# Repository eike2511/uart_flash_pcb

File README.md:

# UART flash PCB

## Features:
- flash µC over UART
	- ESP8266
	- ESP32
	- ATMEGA
	- intigrated slot for ESP8266-01
- intigrated RST and flash button
	- with LEDs and labelling
	- jumper for manual and auto mode
- Reverse polarity protected pin tray
- Three different USB sockets
	- mini USB B
	- micro USB B
	- USB C
- Vcc = 5V  or 3.3V 
	- with LEDs and labelling
	- jumper for selection
	- 5V from USB Bus
	- 3.3V from additional linear regulator in connection with internal regulator of the FT232,  with up to 800mA
- LEDs at TXD and RXD for visual control of the UART connection

## Hardware:
Gerber and drilling data are in the repository. [Component placement](./uart_flash_pcb_ibom.html)

## Software:
No stand-alone software is needed. Use esptool.py or e.g. VS Code for programming.

## Usage:
1. Connect USB
2. Connect the correct jumpers for 5V or 3.3V
3. Connect the jumpers for auto-flash and auto-RST or use the button
4. Connect the device to be flashed or plug in an ESP-01
5. be save the TXD and RXD are crossed

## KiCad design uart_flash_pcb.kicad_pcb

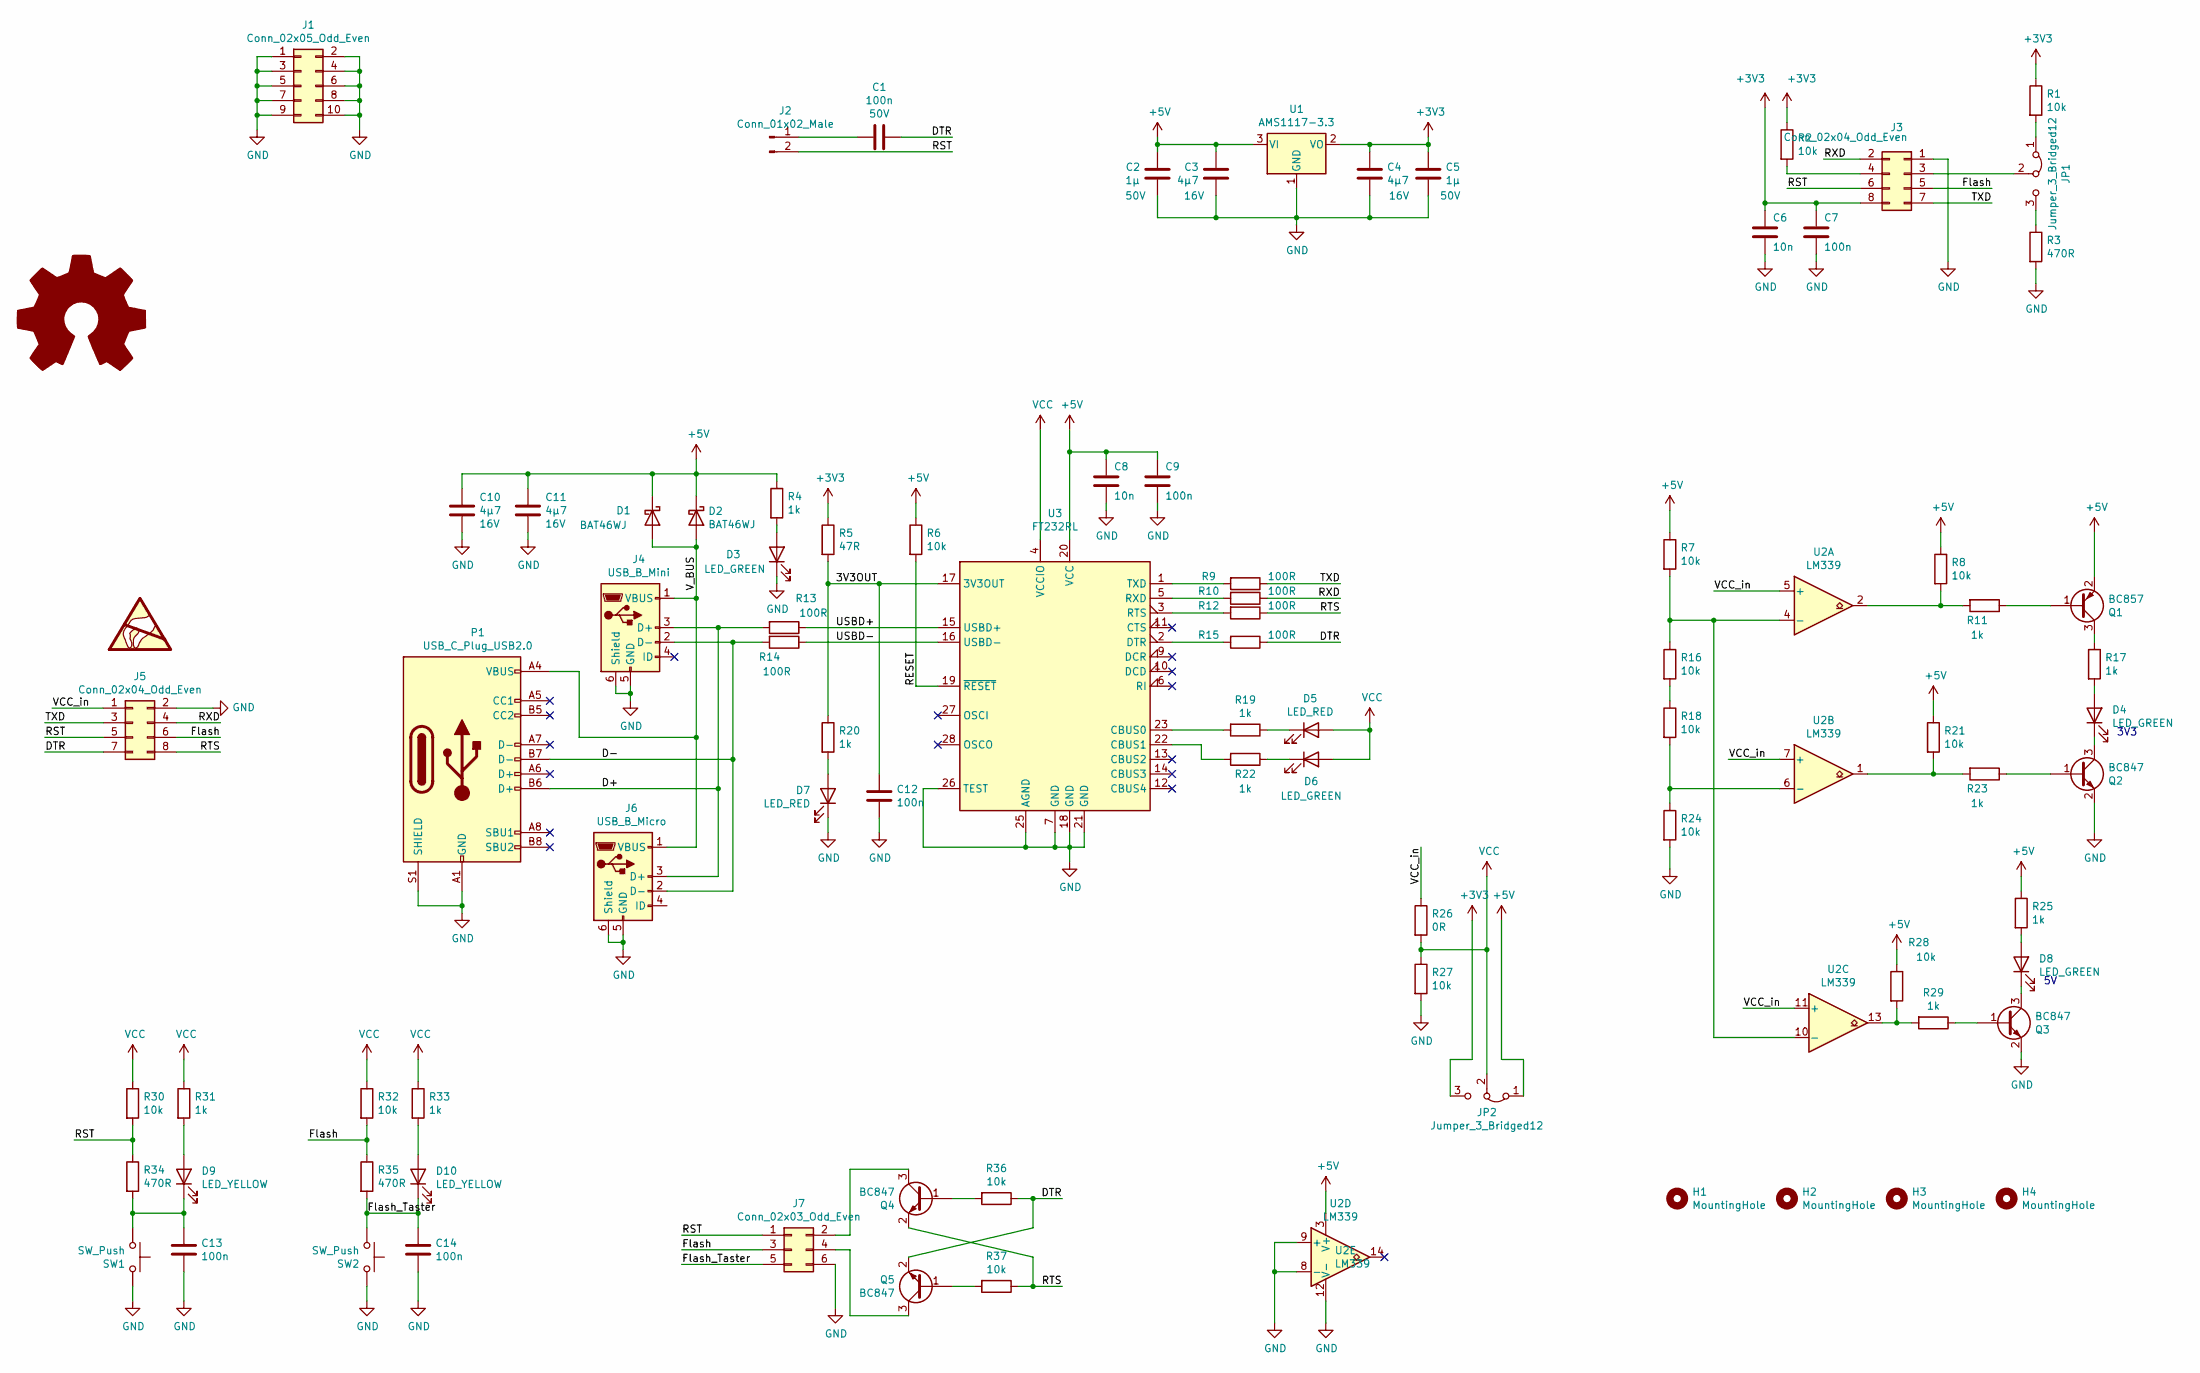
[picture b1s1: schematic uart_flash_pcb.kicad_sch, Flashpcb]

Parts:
C1, C7, C9, C12, C13, C14: 100n; C_0805_2012Metric
C2, C5: 1µ; C_0805_2012Metric
C3, C4, C10, C11: 4µ7; C_1206_3216Metric
C6, C8: 10n; C_0805_2012Metric
D1, D2: BAT46WJ; D_SOD-323
D3, D4, D6, D8: LED_GREEN; LED_0805_2012Metric
D5, D7: LED_RED; LED_0805_2012Metric
D9, D10: LED_YELLOW; LED_0805_2012Metric
H1, H2, H3, H4: MountingHole; MountingHole_3.2mm_M3
J1: Conn_02x05_Odd_Even; PinHeader_2x05_P2.54mm_Vertical
J2: Conn_01x02_Male; PinHeader_1x02_P2.54mm_Vertical
J3: Conn_02x04_Odd_Even; PinSocket_2x04_P2.54mm_Vertical
J4: USB_B_Mini; USB_Mini-B_Wuerth_65100516121_Horizontal
J5: Conn_02x04_Odd_Even; PinHeader_2x04_P2.54mm_Vertical
J6: USB_B_Micro; USB_Micro-B_Molex_47346-0001
J7: Conn_02x03_Odd_Even; PinHeader_2x03_P2.54mm_Vertical
JP1, JP2: Jumper_3_Bridged12; PinHeader_1x03_P2.54mm_Vertical
P1: USB_C_Plug_USB2.0; USB_C_Receptacle_XKB_U262-16XN-4BVC11
Q1: BC857; SOT-23
Q2, Q3, Q4, Q5: BC847; SOT-23
R1, R2, R6, R7, R8, R16, R18, R21, R24, R27, R28, R30, R32, R36, R37: 10k; R_0805_2012Metric
R3, R34, R35: 470R; R_0805_2012Metric
R4, R11, R17, R19, R20, R22, R23, R25, R29, R31, R33: 1k; R_0805_2012Metric
R5: 47R; R_0805_2012Metric
R9, R10, R12, R13, R14, R15: 100R; R_0805_2012Metric
R26: 0R; R_0805_2012Metric
SW1, SW2: SW_Push; SW_Push_SPST_4x3x2
U1: AMS1117-3.3; SOT-223-3_TabPin2
U2: LM339; SOIC-14_3.9x8.7mm_P1.27mm
U3: FT232RL; SSOP-28_5.3x10.2mm_P0.65mm

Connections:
+3V3: C4.1, C5.1, C6.1, C7.1, J3.8, JP2.3 (B), R1.1, R2.1, R5.1, U1.2 (VO)
+5V: C2.1, C3.1, C8.1, C9.1, C10.1, C11.1, D1.1 (K), D2.1 (K), JP2.1 (A), Q1.2 (E), R4.1, R6.1, R7.1, R8.1, R21.1, R25.1, R28.1, U1.3 (VI), U2.3 (V+), U3.20 (VCC)
/3V3OUT: C12.1, R5.2, R20.1, U3.17 (3V3OUT)
/D+: J4.3 (D+), J6.3 (D+), P1.B6 (D+), R13.2
/D-: J4.2 (D-), J6.2 (D-), P1.B7 (D-), R14.2
/DTR: C1.1, J5.7, Q5.2 (E), R15.1, R36.1
/Flash: J3.5, J5.6, J7.3, R32.2, R35.1
/Flash_Taster: C14.1, D10.1 (K), J7.5, R35.2, SW2.1
/RESET: R6.2, U3.19 (~RESET)
/RST: J2.2, J3.6, J5.5, J7.1, R30.2, R34.1
/RTS: J5.8, Q4.2 (E), R12.1, R37.1
/RXD: J3.2, J5.4, R10.1
/TXD: J3.7, J5.3, R9.1
/USBD+: R13.1, U3.15 (USBD+)
/USBD-: R14.1, U3.16 (USBD-)
/VCC_in: J5.1, R26.1, U2.5 (+), U2.7 (+), U2.11 (+)
/V_BUS: D1.2 (A), D2.2 (A), J4.1 (VBUS), J6.1 (VBUS), P1.A4 (VBUS), P1.A9 (VBUS), P1.B4 (VBUS), P1.B9 (VBUS)
GND: C2.2, C3.2, C4.2, C5.2, C6.2, C7.2, C8.2, C9.2, C10.2, C11.2, C12.2, C13.2, C14.2, D3.1 (K), D7.1 (K), J1.1, J1.2, J1.3, J1.4, J1.5, J1.6, J1.7, J1.8, J1.9, J1.10, J3.1, J4.5 (GND), J4.6 (Shield), J5.2, J6.5 (GND), J6.6 (Shield), J7.6, P1.A1 (GND), P1.A12 (GND), P1.B1 (GND), P1.B12 (GND), P1.S1 (SHIELD), Q2.2 (E), Q3.2 (E), R3.2, R24.2, R27.2, SW1.2, SW2.2, U1.1 (GND), U2.8 (-), U2.9 (+), U2.12 (V-), U3.7 (GND), U3.18 (GND), U3.21 (GND), U3.25 (AGND), U3.26 (TEST)
unnamed: C1.2, J2.1
unnamed: C13.1, D9.1 (K), R34.2, SW1.1
unnamed: D3.2 (A), R4.2
unnamed: D4.1 (K), Q2.3 (C)
unnamed: D4.2 (A), R17.2
unnamed: D5.1 (K), R19.1
unnamed: D6.1 (K), R22.1
unnamed: D7.2 (A), R20.2
unnamed: D8.1 (K), Q3.3 (C)
unnamed: D8.2 (A), R25.2
unnamed: D9.2 (A), R31.2
unnamed: D10.2 (A), R33.2
unnamed: J3.3, JP1.2 (C)
unnamed: J3.4, R2.2
unnamed: J7.2, Q4.3 (C)
unnamed: J7.4, Q5.3 (C)
unnamed: JP1.1 (A), R1.2
unnamed: JP1.3 (B), R3.1
unnamed: Q1.1 (B), R11.1
unnamed: Q1.3 (C), R17.1
unnamed: Q2.1 (B), R23.1
unnamed: Q3.1 (B), R29.1
unnamed: Q4.1 (B), R36.2
unnamed: Q5.1 (B), R37.2
unnamed: R9.2, U3.1 (TXD)
unnamed: R10.2, U3.5 (RXD)
unnamed: R8.2, R11.2, U2.2
unnamed: R12.2, U3.3 (RTS)
unnamed: R15.2, U3.2 (DTR)
unnamed: R7.2, R16.1, U2.4 (-), U2.10 (-)
unnamed: R16.2, R18.1
unnamed: R18.2, R24.1, U2.6 (-)
unnamed: R19.2, U3.23 (CBUS0)
unnamed: R21.2, R23.2, U2.1
unnamed: R22.2, U3.22 (CBUS1)
unnamed: R28.2, R29.2, U2.13
VCC: D5.2 (A), D6.2 (A), JP2.2 (C), R26.2, R27.1, R30.1, R31.1, R32.1, R33.1, U3.4 (VCCIO)

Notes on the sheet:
3V3

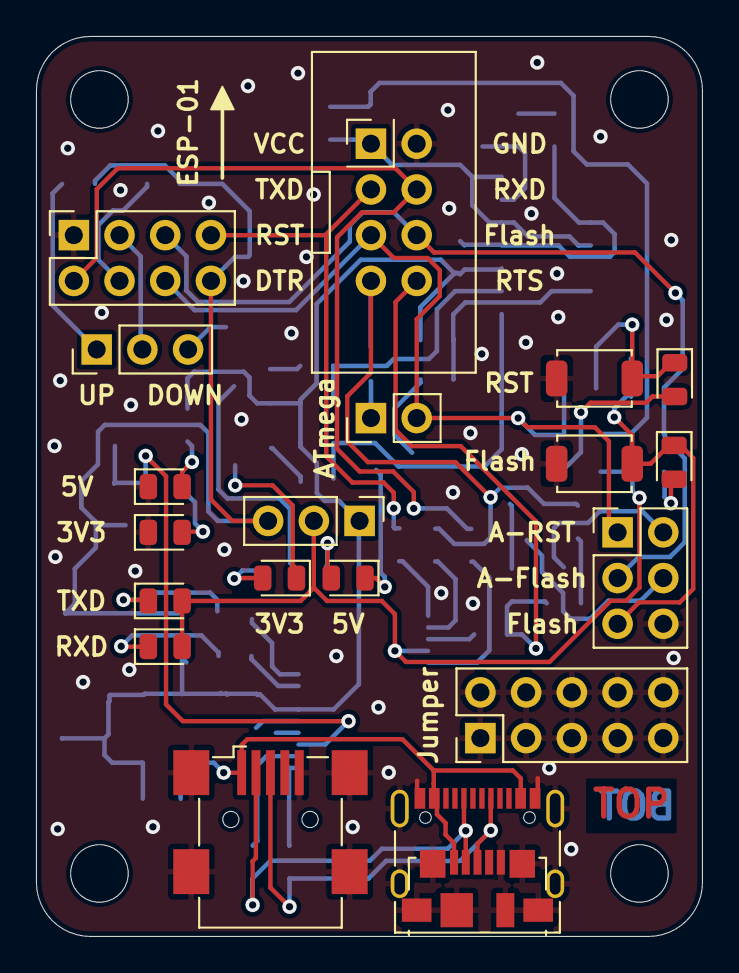
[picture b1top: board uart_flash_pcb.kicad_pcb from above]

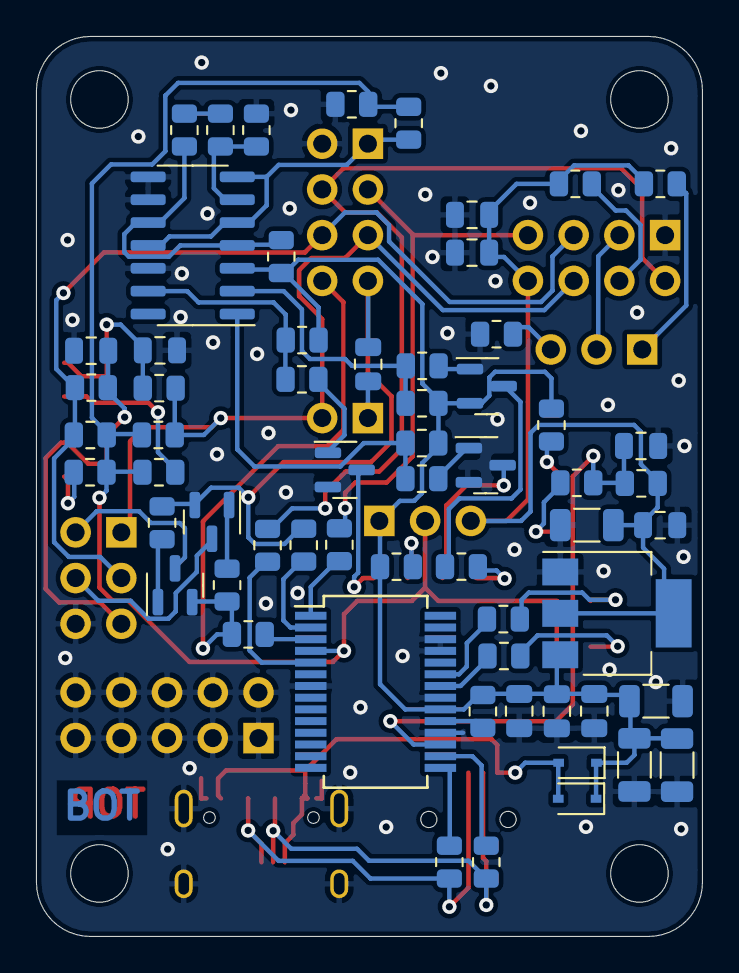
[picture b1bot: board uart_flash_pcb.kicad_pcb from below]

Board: 2 copper layers, 37.0 x 50.0 mm, 85 parts (61 on the bottom side), 55 nets.

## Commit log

2020-12-20 Added demo pictures
2020-12-20 Edit README
    Added some demo pictures to the README file
2020-12-21 Update footprints because of library update
2020-12-21 Added schematic as PDF
2020-12-28 Added 3D models and rendering pictures
2022-05-16 Update 3D printing case
2022-05-16 Edit gitignore
2022-05-16 Update to KiCad v6
